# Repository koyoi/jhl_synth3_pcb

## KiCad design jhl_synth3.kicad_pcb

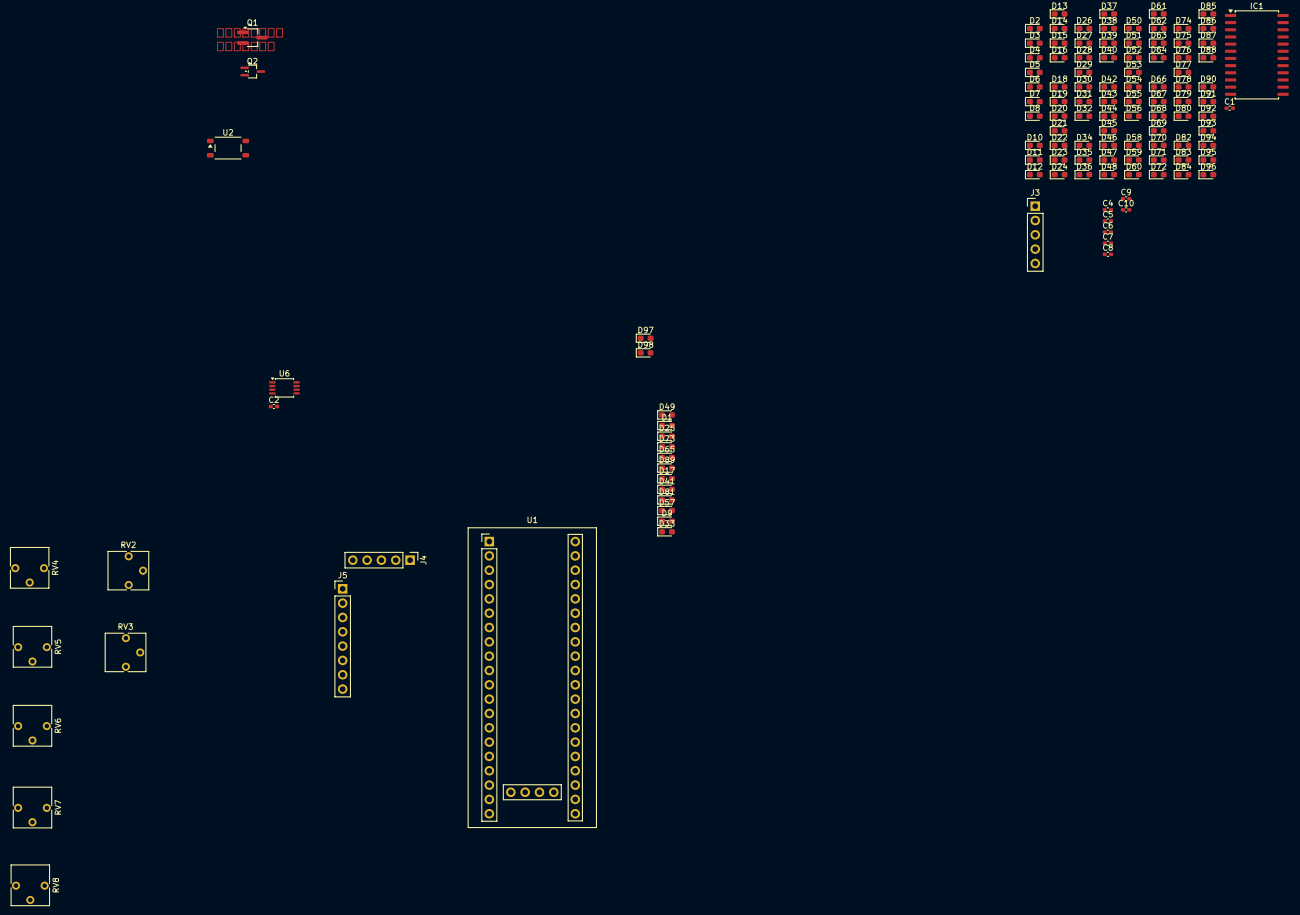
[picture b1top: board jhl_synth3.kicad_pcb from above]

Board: 2 copper layers, 123 parts (0 on the bottom side), 46 nets, no tracks yet.

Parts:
C1, C2, C4, C5, C6, C7, C8, C9, C10: 0.1u; C_0402_1005Metric_Pad0.74x0.62mm_HandSolder
D1, D2, D3, D4, D5, D6, D7, D8, D9, D10, D11, D12, D13, D14, D15, D16, D17, D18, D19, D20, D21, D22, D23, D24, D25, D26, D27, D28, D29, D30, D31, D32, D33, D34, D35, D36, D37, D38, D39, D40, D41, D42, D43, D44, D45, D46, D47, D48, D49, D50, D51, D52, D53, D54, D55, D56, D57, D58, D59, D60, D61, D62, D63, D64, D65, D66, D67, D68, D69, D70, D71, D72, D73, D74, D75, D76, D77, D78, D79, D80, D81, D82, D83, D84, D85, D86, D87, D88, D89, D90, D91, D92, D93, D94, D95, D96, D97, D98: LED_Small_Filled; LED_0603_1608Metric_Pad1.05x0.95mm_HandSolder
IC1: HTK16K33; SOP-24_7.5x15.4mm_P1.27mm
J3: Conn_I2S; PinHeader_1x05_P2.54mm_Vertical
J4: DIN-5; PinHeader_1x05_P2.54mm_Vertical
J5: Conn_LCD; PinHeader_1x08_P2.54mm_Vertical
Q1: NPN 2N3904 SOT-23; TSOT-23_HandSoldering
Q2: NPN 2SC4116 SC-70; SOT-323_SC-70
RV2, RV3, RV4, RV5, RV6, RV7, RV8: R_Potentiometer_US; Potentiometer_Vishay_T73YP_Vertical
U1: YAAJ_WeAct_BlackPill_Part_Like; YAAJ_WeAct_BlackPill_SWD_2
U2: TLP127; Toshiba_SOIC-4-6_4.4x3.6mm_P1.27mm
U6: PCA9306DP; TSSOP-8_3x3mm_P0.65mm

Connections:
+3.3V: J3.5, J5.1, J5.8, RV2.1, RV3.1, RV4.1, RV5.1, RV6.1, RV7.1, RV8.1, U1.20 (3V3), U1.38 (3V3), U6.2 (VREF1)
+5V: C2.1, IC1.24 (VDD), U1.18 (5V), U1.40 (5V)
ADC1: C4.1, RV2.2, U1.27 (PA1)
ADC2: C5.1, RV3.2, U1.28 (PA2)
ADC3: C6.1, RV4.2, U1.29 (PA3)
ADC4: C7.1, RV5.2, U1.30 (PA4)
ADC5: C8.1, RV6.2, U1.31 (PA5)
ADC6: C9.1, RV7.2, U1.32 (PA6)
ADC7: C10.1, RV8.2, U1.33 (PA7)
GND: C1.2, C2.2, C4.2, C5.2, C6.2, C7.2, C8.2, C9.2, C10.2, D97.1 (K), D98.1 (K), IC1.1 (VSS), J3.4, J5.2, Q1.3 (E), Q2.3 (E), RV2.3, RV3.3, RV4.3, RV5.3, RV6.3, RV7.3, RV8.3, U1.19 (GND), U1.39 (GND), U2.4, U6.1 (GND)
I2C_SCL: U1.14 (PB6), U6.3 (SCL1)
I2C_SCL5: IC1.22 (SCL), U6.6 (SCL2)
I2C_SDA: U1.15 (PB7), U6.4 (SDA1)
I2C_SDA5: IC1.23 (SDA), U6.5 (SDA2)
I2S_CK: J3.1, U1.11 (PB3)
I2S_SD: J3.2, U1.13 (PB5)
I2S_WS: J3.3, U1.10 (PA15)
LCD_A0: J5.5, U1.17 (PB9)
LCD_RESET: J5.4, U1.12 (PB4)
LED_C0: D1.1 (K), D9.1 (K), D17.1 (K), D25.1 (K), D33.1 (K), D41.1 (K), D49.1 (K), D57.1 (K), D65.1 (K), D73.1 (K), D81.1 (K), D89.1 (K), IC1.2 (COM0/AD)
LED_C1: D2.1 (K), D10.1 (K), D18.1 (K), D26.1 (K), D34.1 (K), D42.1 (K), D50.1 (K), D58.1 (K), D66.1 (K), D74.1 (K), D82.1 (K), D90.1 (K), IC1.3 (COM1/KS0)
LED_C2: D3.1 (K), D11.1 (K), D19.1 (K), D27.1 (K), D35.1 (K), D43.1 (K), D51.1 (K), D59.1 (K), D67.1 (K), D75.1 (K), D83.1 (K), D91.1 (K), IC1.4 (COM2/KS1)
LED_C3: D4.1 (K), D12.1 (K), D20.1 (K), D28.1 (K), D36.1 (K), D44.1 (K), D52.1 (K), D60.1 (K), D68.1 (K), D76.1 (K), D84.1 (K), D92.1 (K), IC1.5 (COM3/KS2)
LED_C4: D5.1 (K), D13.1 (K), D21.1 (K), D29.1 (K), D37.1 (K), D45.1 (K), D53.1 (K), D61.1 (K), D69.1 (K), D77.1 (K), D85.1 (K), D93.1 (K), IC1.6 (COM4)
LED_C5: D6.1 (K), D14.1 (K), D22.1 (K), D30.1 (K), D38.1 (K), D46.1 (K), D54.1 (K), D62.1 (K), D70.1 (K), D78.1 (K), D86.1 (K), D94.1 (K), IC1.7 (COM5)
LED_C6: D7.1 (K), D15.1 (K), D23.1 (K), D31.1 (K), D39.1 (K), D47.1 (K), D55.1 (K), D63.1 (K), D71.1 (K), D79.1 (K), D87.1 (K), D95.1 (K), IC1.8 (COM6)
LED_C7: D8.1 (K), D16.1 (K), D24.1 (K), D32.1 (K), D40.1 (K), D48.1 (K), D56.1 (K), D64.1 (K), D72.1 (K), D80.1 (K), D88.1 (K), D96.1 (K), IC1.9 (COM7)
LED_R0: D1.2 (A), D2.2 (A), D3.2 (A), D4.2 (A), D5.2 (A), D6.2 (A), D7.2 (A), D8.2 (A), IC1.21 (ROW0/A1)
LED_R1: D9.2 (A), D10.2 (A), D11.2 (A), D12.2 (A), D13.2 (A), D14.2 (A), D15.2 (A), D16.2 (A), IC1.20 (ROW1/A0)
LED_R2: D17.2 (A), D18.2 (A), D19.2 (A), D20.2 (A), D21.2 (A), D22.2 (A), D23.2 (A), D24.2 (A), IC1.19 (ROW2/K1)
LED_R3: D25.2 (A), D26.2 (A), D27.2 (A), D28.2 (A), D29.2 (A), D30.2 (A), D31.2 (A), D32.2 (A), IC1.18 (ROW3/K2)
LED_R4: D33.2 (A), D34.2 (A), D35.2 (A), D36.2 (A), D37.2 (A), D38.2 (A), D39.2 (A), D40.2 (A), IC1.17 (ROW4/K3)
LED_R5: D41.2 (A), D42.2 (A), D43.2 (A), D44.2 (A), D45.2 (A), D46.2 (A), D47.2 (A), D48.2 (A), IC1.16 (ROW5/K4)
LED_R6: D49.2 (A), D50.2 (A), D51.2 (A), D52.2 (A), D53.2 (A), D54.2 (A), D55.2 (A), D56.2 (A), IC1.15 (ROW6/K5)
LED_R7: D57.2 (A), D58.2 (A), D59.2 (A), D60.2 (A), D61.2 (A), D62.2 (A), D63.2 (A), D64.2 (A), IC1.14 (ROW7/K6)
LED_R8: D65.2 (A), D66.2 (A), D67.2 (A), D68.2 (A), D69.2 (A), D70.2 (A), D71.2 (A), D72.2 (A), IC1.13 (ROW8/K7)
LED_R9: D73.2 (A), D74.2 (A), D75.2 (A), D76.2 (A), D77.2 (A), D78.2 (A), D79.2 (A), D80.2 (A), IC1.12 (ROW9/K8)
LED_R10: D81.2 (A), D82.2 (A), D83.2 (A), D84.2 (A), D85.2 (A), D86.2 (A), D87.2 (A), D88.2 (A), IC1.11 (ROW10/K9)
LED_R11: D89.2 (A), D90.2 (A), D91.2 (A), D92.2 (A), D93.2 (A), D94.2 (A), D95.2 (A), D96.2 (A), IC1.10 (ROW11/K10/INT)
unnamed: J4.5, U2.3
unnamed: Q1.2 (B), Q2.2 (B)
unnamed: C1.1, U6.7 (VREF2), U6.8 (EN)
SPI_MOSI: J5.6, U1.4 (PB15)
SPI_SCK: J5.7, U1.2 (PB13)
SPI_nSS: J5.3, U1.1 (PB12)
midi_in: Q1.1 (C), Q2.1 (C), U1.7 (PA10)

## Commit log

2026-04-29 initial
2026-04-30 LED並べた、だけ。
2026-05-10 日々更新
